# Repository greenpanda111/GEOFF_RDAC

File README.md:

# GEOFF
 3rd Year Engineering Module

 GEOFF is a 2 wheeled skid steered maze solving robot consisting of:
 2 motors with an ecoder each
 The encoders are wired to the ARB board using the expected pins as well as spare GPIO for the ultrasonics.
 
 4 IR sensors
 Two on the front for wall alignment using triganometry to calculate the angle to turn and for a wider field of view.
 One on either side of the robot for measuring the distance to the left and right of the robot.

 2 Ultrasonic sensors
 These are not currently utilised but my CAD design allows for them to be freely rotated so could be added for improved mapping capabilities in future.
 
 4 LED NeoPixel panels
 These form a 16x16 LED matrix to display live mapping of obstacles and route travelled along with current location and heading.
 The graphics library (All three NeoPixel libraries are created by Adafruit) used can allow for easy debugging. For example: writing the current angle onto the screen to test if it is being updated correctly as the robot turns.

 The Neopixel matrix can be controlled with one 5V signal pin. To achieve this, I had to design a level shifter to control it with the arduinos 3V3 signal

 2 Microswitches attached to the front corners of the robot to create a front bumper
 These prevent the robot from crashing into obstacles that the front IRs did not detect or catching on corners

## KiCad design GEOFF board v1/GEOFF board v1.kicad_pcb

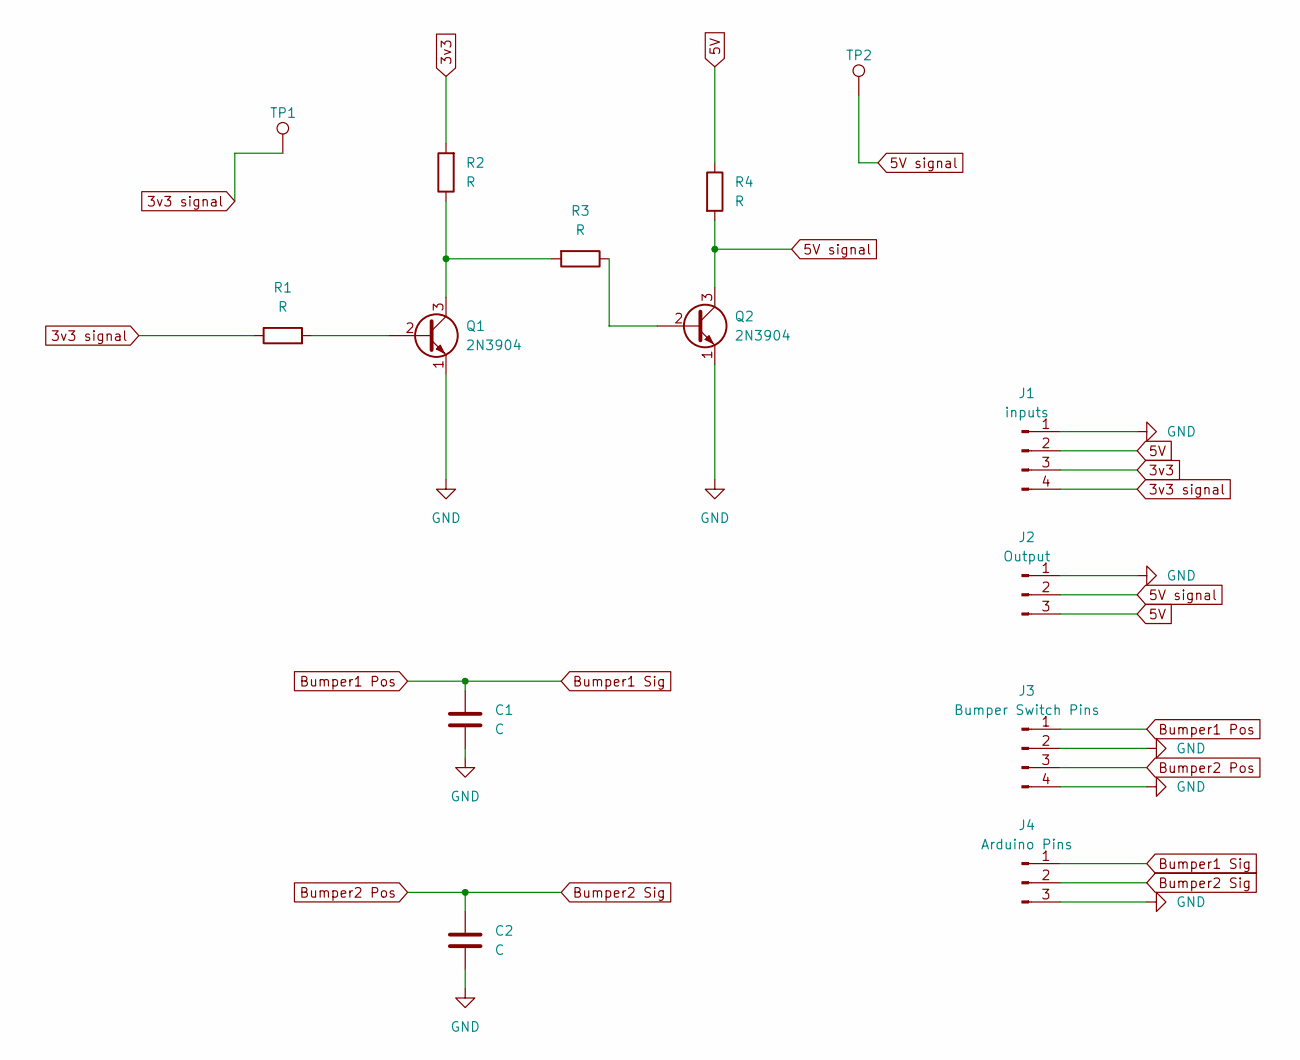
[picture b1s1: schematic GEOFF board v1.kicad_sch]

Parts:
C1, C2: C; CP_Radial_D7.5mm_P2.50mm
J1: inputs; PinHeader_1x04_P2.54mm_Vertical
J2: Output; PinHeader_1x03_P2.54mm_Vertical
J3: Bumper Switch Pins; PinHeader_1x04_P2.54mm_Vertical
J4: Arduino Pins; PinHeader_1x03_P2.54mm_Vertical
Q1, Q2: 2N3904; TO-92_Inline
R1, R2, R3, R4: R; R_0603_1608Metric_Pad0.98x0.95mm_HandSolder
TP1, TP2: TestPoint; TestPoint_THTPad_D1.0mm_Drill0.5mm

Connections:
3v3: J1.3, R2.2
3v3 signal: J1.4, R1.1, TP1.1
5V: J1.2, J2.3, R4.1
5V signal: J2.2, Q2.3 (C), R4.2, TP2.1
Bumper1 Pos: C1.1, J3.1, J4.1
Bumper2 Pos: C2.1, J3.3, J4.2
GND: C1.2, C2.2, J1.1, J2.1, J3.2, J3.4, J4.3, Q1.1 (E), Q2.1 (E)
unnamed: Q1.2 (B), R1.2
unnamed: Q1.3 (C), R2.1, R3.2
unnamed: Q2.2 (B), R3.1

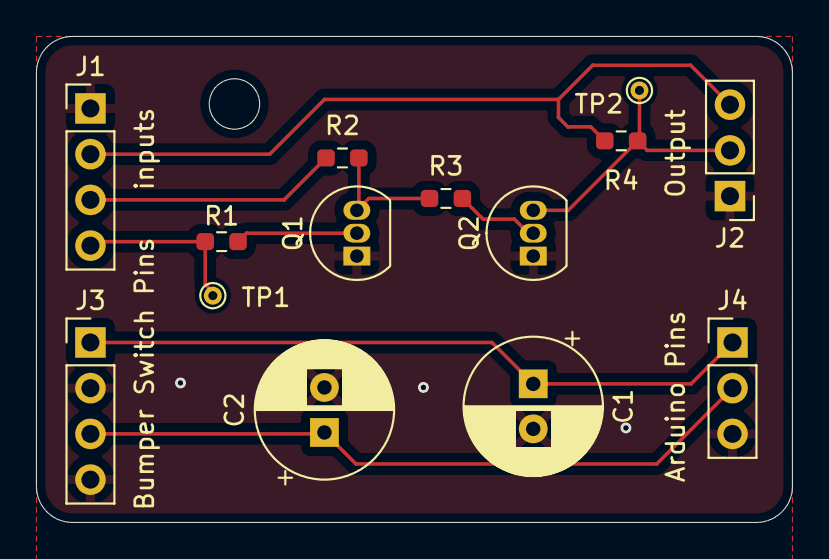
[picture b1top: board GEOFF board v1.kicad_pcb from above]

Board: 2 copper layers, 42.0 x 27.0 mm, 14 parts (0 on the bottom side), 10 nets.

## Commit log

2024-10-29 Migration to VS
2024-10-29 Initial boundary detection
2024-10-31 Enoder Class Working
2024-11-04 Encoders
2024-11-08 NeoPixel First
2024-11-15 LED Bitmaps
2024-11-15 Shitty encoder code
2024-11-18 Refactored Encoders
2024-11-18 bumpers
2024-11-19 Encoders in Controller
2024-11-19 Rotation with angles
2024-11-20 Tidied up
2024-11-20 PID beginnings
2024-11-21 Velocity
2024-11-21 Updated Bumpers
2024-11-22 Debounced bumpers
2024-11-27 Moved root directory
2024-11-28 PID functional
2024-12-06 PID to be calibrated
2024-12-13 PID calibration
2024-12-15 Movement refactored
2025-01-08 Count reset to float
2025-01-09 Working P controller
2025-01-10 Maze solving and wall alignment
2025-01-11 IR refactored
2025-01-11 Wall Alignment Integrated
2025-01-12 Obstacle Avoiding
2025-01-12 Map Location Tracking
2025-01-13 Obstacles and Empty Occupancy Grid
2025-01-13 Occupancy grid tracking
2025-01-13 Turn Bools
2025-01-14 Heading displayed on map
2025-01-14 Solves Maze
2025-01-14 Half commented
2025-01-14 Dead End Escape
2025-01-15 Commented
2025-01-15 ReadMe
2025-01-15 CAD Included
2025-01-15 CAD and PPT
2025-01-16 Assembly Fixed. Presentation Finished. PCB added
